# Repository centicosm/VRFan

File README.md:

# VRFan
VRFan consists of firmware, schematic, and PCB for an adapter used to convert a standard 'dumb' USB fan into a HID device, with the intention of doing something with the USB port available on the Oculus Rift DevKit 2 HMD.
As a HID device, the fan is software controllable and can be turned on or off at times appropriate for a particular VR scene.

Programs to test device functionality for both windows (in C#) and Linux (in C) are in the WindowsApp and VRFan_LinuxTester directories respectively.

The device is powered over USB and utilizes a PIC16F1455 as the controller and MPLab/XC8 as the toolchain.  Schematic and PCB are in KiCad.

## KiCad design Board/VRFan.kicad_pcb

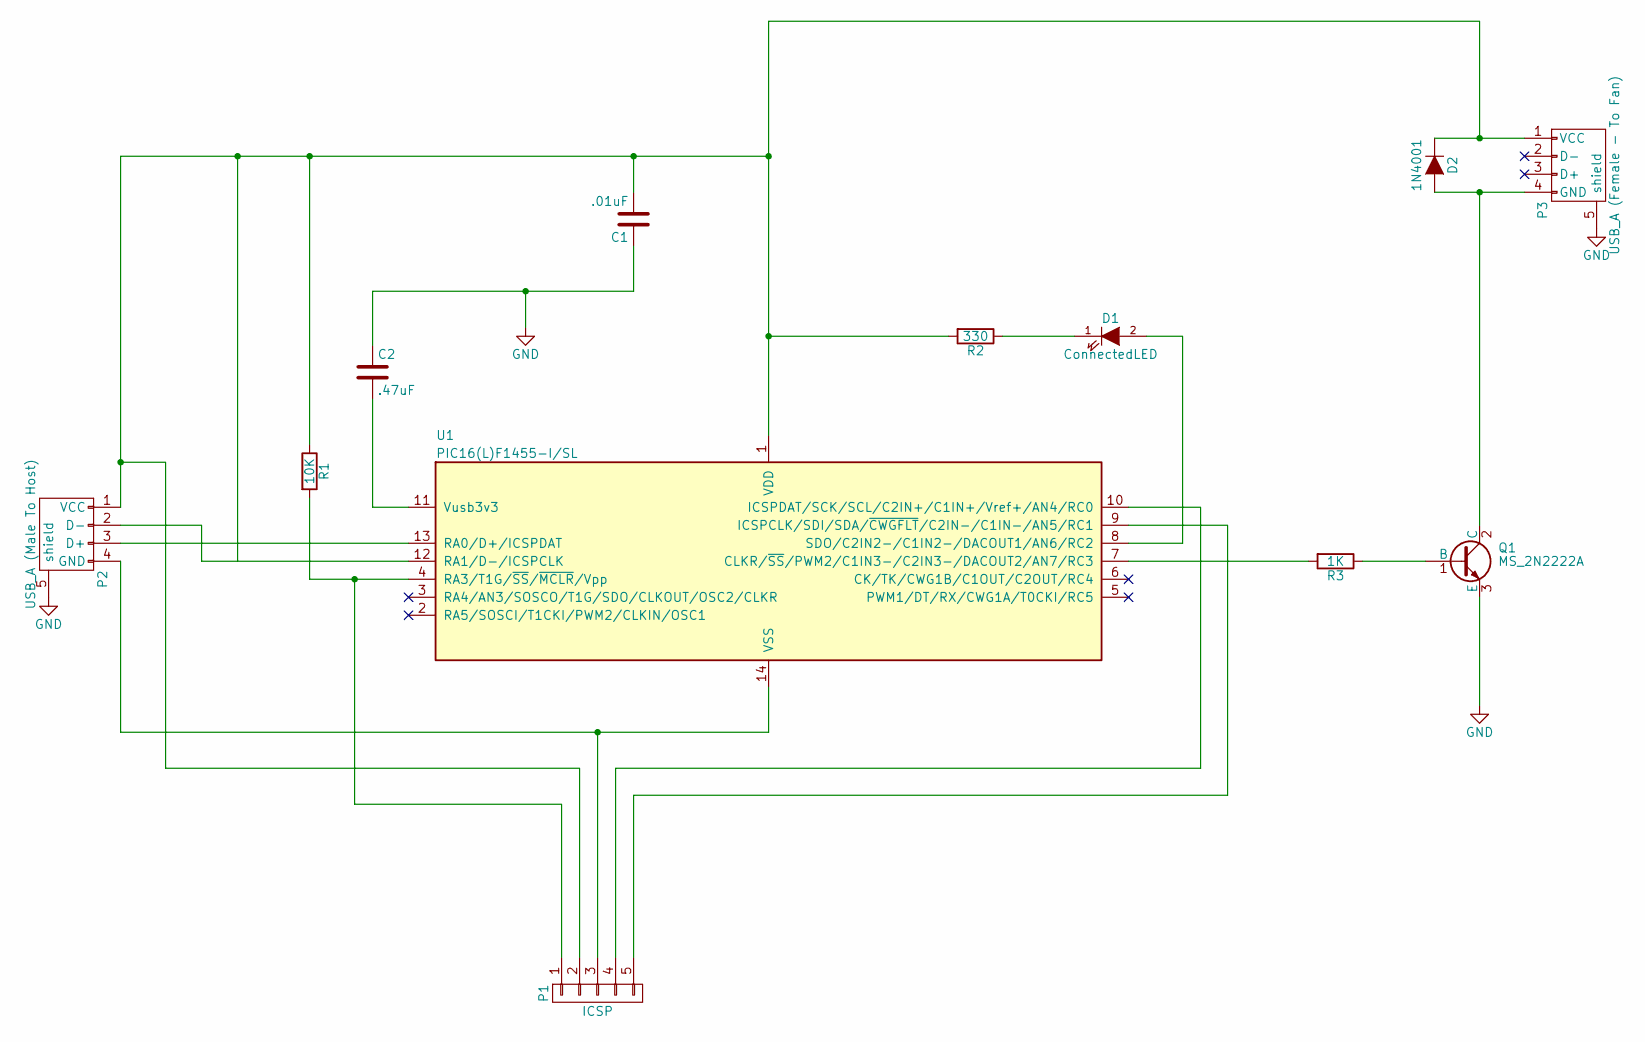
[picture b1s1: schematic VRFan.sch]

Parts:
C1: .01uF; C_Disc_D7.5_P5
C2: .47uF; C_Disc_D6_P5
D1: ConnectedLED; LED-3MM
D2: 1N4001; Diode_DO-41_SOD81_Horizontal_RM10
P1: ICSP; Pin_Header_Angled_1x05
P2: USB_A (Male To Host); Pin_Header_Angled_1x05
P3: USB_A (Female - To Fan); USB_A
Q1: MS_2N2222A
R1: 10K; Resistor_Horizontal_RM10mm
R2: 330; Resistor_Horizontal_RM10mm
R3: 1K; Resistor_Horizontal_RM10mm
U1: PIC16(L)F1455-I/SL

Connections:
GND: C1.1, C2.1, P2.5 (shield), P3.5 (shield), Q1.3 (E)
unnamed: C1.2, D2.1 (K), P1.2, P2.1 (VCC), P3.1 (VCC), R1.1, R2.2, U1.1 (VDD)
unnamed: C2.2, U1.11 (Vusb3v3)
unnamed: D1.1 (K), R2.1
unnamed: D1.2 (A), U1.8 (SDO/C2IN2-/C1IN2-/DACOUT1/AN6/RC2)
unnamed: D2.2 (A), P3.4 (GND), Q1.2 (C)
unnamed: P1.1, R1.2, U1.4 (RA3/T1G/~SS~/~MCLR~/Vpp)
unnamed: P1.3, P2.4 (GND), U1.14 (VSS)
unnamed: P1.4, U1.10 (ICSPDAT/SCK/SCL/C2IN+/C1IN+/Vref+/AN4/R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)
unnamed: P1.5, U1.9 (ICSPCLK/SDI/SDA/~CWGFLT~/C2IN-/C1IN-/AN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)
unnamed: P2.2 (D-), U1.12 (RA1/D-/ICSPCLK)
unnamed: P2.3 (D+), U1.13 (RA0/D+/ICSPDAT)
unnamed: Q1.1 (B), R3.1
unnamed: R3.2, U1.7 (CLKR/~SS~/PWM2/C1IN3-/C2IN3-/DACOUT2/AN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)

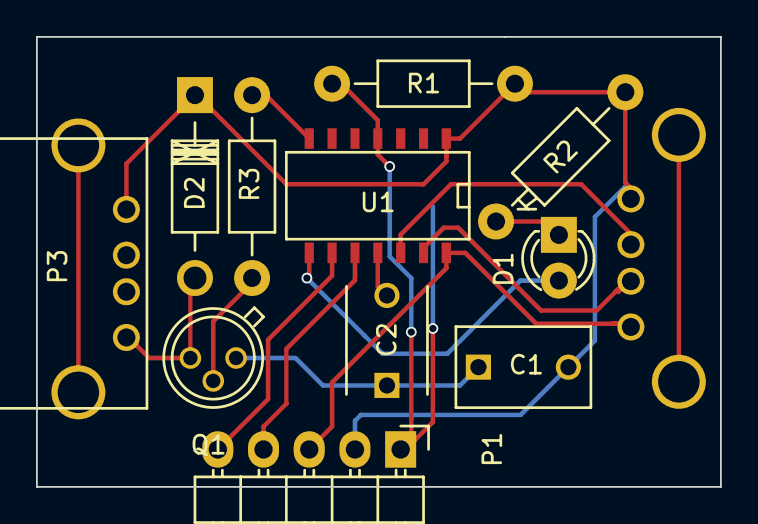
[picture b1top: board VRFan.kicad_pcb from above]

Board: 2 copper layers, 38.0 x 25.0 mm, 12 parts (1 on the bottom side), 14 nets.

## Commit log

2015-12-23 :octocat: Added .gitattributes & .gitignore files
2015-12-23 Added BOM
